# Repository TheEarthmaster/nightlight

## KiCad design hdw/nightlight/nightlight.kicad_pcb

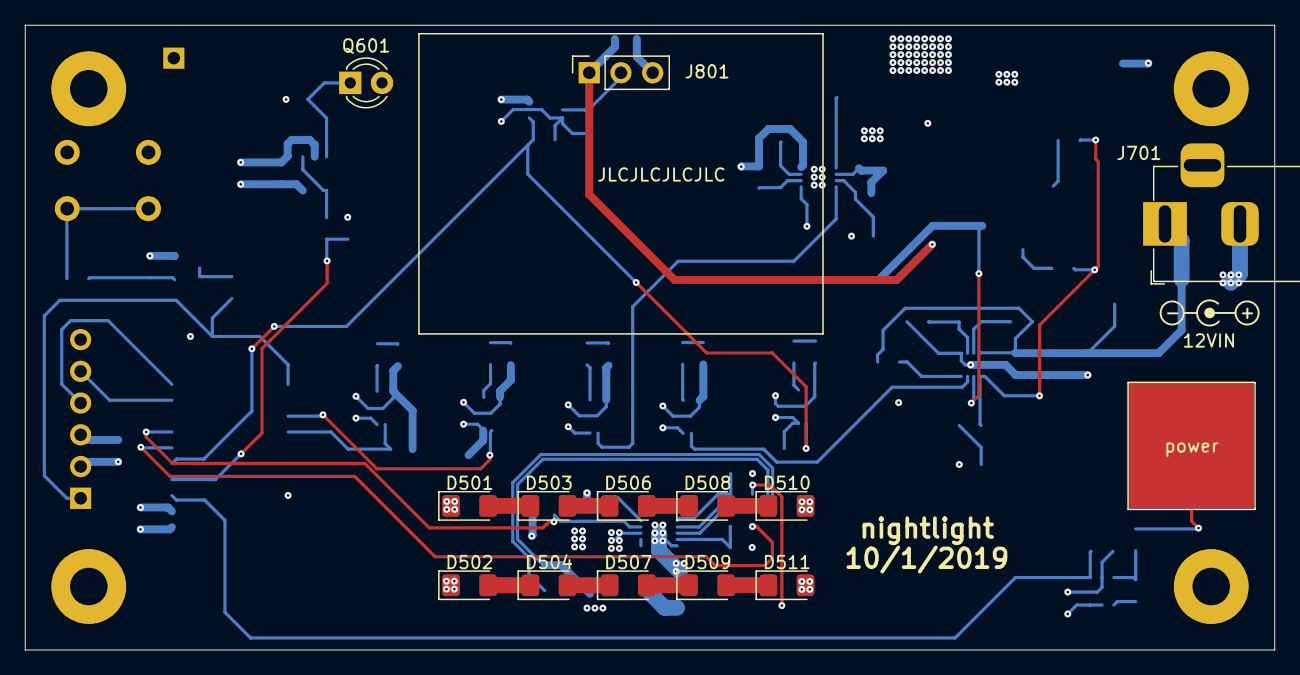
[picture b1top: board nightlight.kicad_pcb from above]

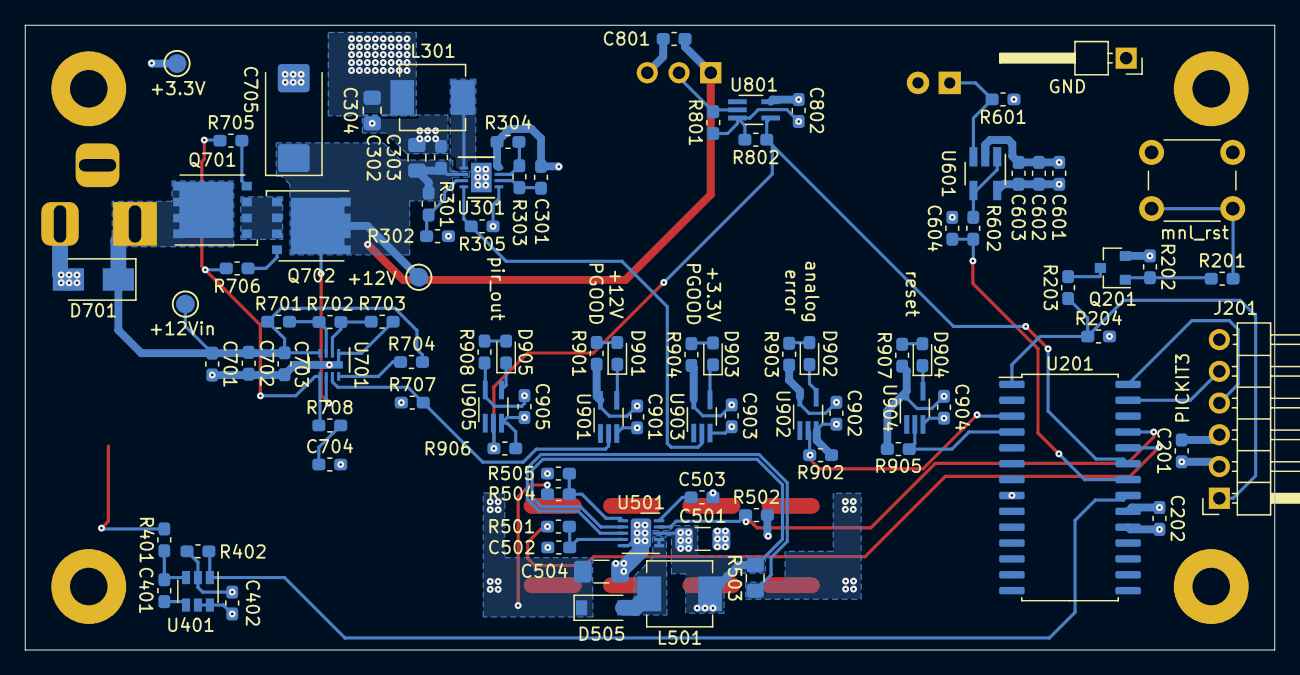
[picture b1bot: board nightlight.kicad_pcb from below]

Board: 4 copper layers, 100.0 x 50.0 mm, 112 parts (94 on the bottom side), 61 nets.

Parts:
C201, C202, C303, C401, C402, C502, C601, C701, C704, C801, C802, C901, C902, C903, C904, C905: 0.1uF; C_0603_1608Metric_Pad1.05x0.95mm_HandSolder
C301: 2.2uF; C_0603_1608Metric_Pad1.05x0.95mm_HandSolder
C302: 22uF; C_0805_2012Metric_Pad1.15x1.40mm_HandSolder
C304: 47uF; C_0805_2012Metric_Pad1.15x1.40mm_HandSolder
C501, C504: 4.7uF; C_1206_3216Metric_Pad1.42x1.75mm_HandSolder
C503, C602, C604, C702: 10nF; C_0603_1608Metric_Pad1.05x0.95mm_HandSolder
C603, C703: 1nF; C_0603_1608Metric_Pad1.05x0.95mm_HandSolder
C705: 100uF; CP_EIA-7343-31_Kemet-D_Pad2.25x2.55mm_HandSolder
D501, D502, D503, D504, D506, D507, D508, D509, D510, D511: warm white; LED_1206_3216Metric_Pad1.42x1.75mm_HandSolder
D505: MBR0530; D_SOD-123
D701: 24V; D_SMA
D901, D903, D905: green; LED_0603_1608Metric_Pad1.05x0.95mm_HandSolder
D902, D904: red; LED_0603_1608Metric_Pad1.05x0.95mm_HandSolder
H1001, H1002, H1003, H1004: MountingHole; MountingHole_3mm_Pad
J201: PICKIT3; PICKIT3_Header
J701: +12V IN AUX; BarrelJack_Horizontal
J801: PIR Sensor; pirsensor
L301: 4.7uH; L_Vishay_IHLP-2020
L501: 3.3uH; L_Vishay_IHLP-2020
Q201: 2N7002; SOT-23
Q601: BPW85A; LED_D3.0mm_Clear
Q701, Q702: IPC100N04S51R7ATMA1; TDSON-8-1
R201, R203, R705, R706: 10; R_0603_1608Metric_Pad1.05x0.95mm_HandSolder
R202, R204, R301, R303, R304, R305, R402, R502, R601, R707, R801, R802, R902, R905, R906: 10k; R_0603_1608Metric_Pad1.05x0.95mm_HandSolder
R302: 1.2k; R_0603_1608Metric_Pad1.05x0.95mm_HandSolder
R401, R602: 499; R_0603_1608Metric_Pad1.05x0.95mm_HandSolder
R501: 5.1K; R_0603_1608Metric_Pad1.05x0.95mm_HandSolder
R503: .18; R_0805_2012Metric_Pad1.15x1.40mm_HandSolder
R504: 15.8K; R_0603_1608Metric_Pad1.05x0.95mm_HandSolder
R505: 1.07k; R_0603_1608Metric_Pad1.05x0.95mm_HandSolder
R701: 6.04M; R_0603_1608Metric_Pad1.05x0.95mm_HandSolder
R702: 86.6k; R_0603_1608Metric_Pad1.05x0.95mm_HandSolder
R703: 243k; R_0603_1608Metric_Pad1.05x0.95mm_HandSolder
R704: 100k; R_0603_1608Metric_Pad1.05x0.95mm_HandSolder
R708: 5.1k; R_0603_1608Metric_Pad1.05x0.95mm_HandSolder
R901, R903, R904, R907, R908: 1k; R_0603_1608Metric_Pad1.05x0.95mm_HandSolder
SW201: MRST; SW_PUSH_6mm
SW401: Cap_Touch; Capacitive_Touch_Pad_Wide
TP301, TP702, TP703: TP; Test_Point
TP701: TP; PinHeader_1x01_P2.54mm_Horizontal
U201: PIC16F1518-ISO; SOIC-28W_7.5x17.9mm_P1.27mm
U301: LTC3624DD; DFN-8-1EP_3x3mm_P0.5mm_EP1.66x2.38mm
U401: AT42QT1010-TSHR; SOT-23-6
U501: LT1618DD; DFN-10-1EP_3x3mm_P0.5mm_EP1.65x2.38mm
U601: OPA340NA; SOT-23-5_HandSoldering
U701: LTC4365DDB; DFN-8-1EP_2x3mm_P0.5mm_EP0.61x2.2mm
U801: 74LVC1G17; SOT-353_SC-70-5_Handsoldering
U901, U902, U903, U904, U905: 74LVC1G06_Power; SOT-353_SC-70-5_Handsoldering

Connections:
+3V3: C201.1, C202.1, C304.1, C402.1, C501.1, C601.1, C602.1, C603.1, C802.1, C901.1, C902.1, C903.1, C904.1, C905.1, J201.2, L301.2, L501.1, R204.2, R305.1, R503.2, R601.1, R707.1, R901.1, R903.1, R904.1, R905.1, R907.1, R908.1, SW201.1, TP301.1, U201.20, U301.5, U401.5, U401.6, U501.2, U501.8, U601.5, U801.5, U901.5, U902.5, U903.5, U904.5, U905.5
+12V: C302.1, C303.1, C705.1, C801.1, J801.1, Q702.5, R301.1, TP703.1, U301.2, U701.6
+12Vin: C701.1, C702.1, C703.1, D701.1, J701.1, Q701.5, R701.1, R704.1, TP702.1, U701.4
Cap_Touch_Power: R402.1, U201.21, U401.1
GND: C201.2, C202.2, C301.2, C302.2, C303.2, C304.2, C402.2, C501.2, C502.2, C503.2, C504.2, C601.2, C602.2, C603.2, C604.2, C701.2, C702.2, C703.2, C704.2, C705.2, C801.2, C802.2, C901.2, C902.2, C903.2, C904.2, C905.2, D701.2, J201.3, J701.2, J701.3, J801.3, Q201.2, Q601.2, R202.1, R302.2, R304.2, R402.2, R502.2, R505.2, R703.2, R801.2, R802.2, R902.2, R906.2, TP701.1, U201.8, U201.19, U301.8, U301.9, U401.2, U501.5, U501.11, U601.2, U701.1, U701.9, U801.3, U901.3, U902.3, U903.3, U904.3, U905.3
ICDCLK: J201.5, U201.27
ICDDAT: J201.4, U201.28
unnamed: C301.1, R303.1, U301.6
unnamed: C401.1, R401.1, U401.3
unnamed: C401.2, U401.4
unnamed: C502.1, R501.1, U501.4
unnamed: C503.1, U501.10
unnamed: C504.1, D505.1, D510.2, D511.2, R504.1
unnamed: C704.1, R708.2
unnamed: D501.1, D502.1, R503.1, U501.3
unnamed: D501.2, D503.1
unnamed: D502.2, D504.1
unnamed: D503.2, D506.1
unnamed: D504.2, D507.1
unnamed: D505.2, L501.2, U501.6, U501.7
unnamed: D506.2, D508.1
unnamed: D507.2, D509.1
unnamed: D508.2, D510.1
unnamed: D509.2, D511.1
unnamed: D901.1, U901.4
unnamed: D901.2, R901.2
unnamed: D902.1, U902.4
unnamed: D902.2, R903.2
unnamed: D903.1, U903.4
unnamed: D903.2, R904.2
unnamed: D904.1, U904.4
unnamed: D904.2, R907.2
unnamed: D905.1, U905.4
unnamed: D905.2, R908.2
unnamed: J801.2, R801.1, U801.2
unnamed: L301.1, U301.1
unnamed: Q201.1, R201.1, R202.2
unnamed: Q201.3, R203.2
unnamed: Q601.1, R601.2, U601.3
unnamed: Q701.1, Q701.2, Q701.3, Q702.1, Q702.2, Q702.3
unnamed: Q701.4, R705.2
unnamed: Q702.4, R706.1
unnamed: R201.2, SW201.2
unnamed: R301.2, R302.1, U301.3
unnamed: R303.2, R304.1, U301.7
unnamed: R401.2, SW401.1
unnamed: R504.2, R505.1, U501.1
unnamed: R602.2, U601.1, U601.4
unnamed: R701.2, R702.1, U701.3
unnamed: R702.2, R703.1, U701.2
unnamed: R704.2, U701.8
unnamed: R705.1, R706.2, R708.1, U701.5
POS3P3_PGOOD: R305.2, U301.4, U903.2
POS12_PGOOD: R707.2, U701.7, U901.2
analog_error: R902.1, U201.3, U902.2
led_enable: R502.1, U201.25, U501.9
led_pwm: R501.2, U201.24
light_level_adc: C604.1, R602.1, U201.22
pir_out: R802.1, R906.1, U201.23, U801.4, U905.2
reset: R905.2, U201.4, U904.2
~MCLR: J201.1, R203.1, R204.1, U201.1

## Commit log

2019-08-28 Began project, drew a few schematic sheets
2019-09-05 Added ambient light sensor, LED driver
2019-09-18 finished schematic
2019-09-24 added Digi-Key p/n
2019-09-25 Assigned footprints
2019-09-25 Started arranging components on PCB
2019-09-25 Arranged footprints for power button, buck converter
2019-09-29 Finished arranging components on PCB
2019-09-29 Placed components on virtual board
2019-09-29 Started routing, minor schematic changes
2019-10-02 finished PCD
2019-11-04 started coding
2019-11-08 fixed gitignore
2019-11-08 Got PWM fading working
2019-11-15 Added IOC stuff
2019-11-15 PIR sensor working
2019-11-17 finished fmw project
